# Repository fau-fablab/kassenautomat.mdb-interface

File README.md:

kassenautomat.mdb-interface
===========================

MDB to USB Interface für Münzwechsler-Ansteuerung

FTDI-Konfiguration
------------------
 * es kommt ein FT232RL zum Einsatz
 * Tool für Linux: https://github.com/mehlis/ft232r_prog.git
 * sonst FT_PROG
 * Linuxzeile: `./ft232r_prog --product 'MDB Interface' --manufacturer 'FAU FabLab' --cbus0 TxLED --cbus1 RxLED --cbus2 Clk12`

Atmel
-----
  * `make fuse` (zur Zeit für external clock via FTDI)
  *  http://www.engbedded.com/fusecalc/
  *  Wenn die Fuses auf externen Takt gesetzt sind, läuft der Chip nur, solange kein USB suspend ist - screen offen halten! (wirklich? nicht jeder hat usb autosuspend an.)
  * `make program`

Sicherung 12V-Schiene
---------------------
  * im worst case sollte eine 5A mtltrg. Sicherung für die 12V-Schiene reichen

Aktueller Stand Platine
-----------------------
  * Kommunikation Atmel <-> PC -> MDB geht, MDB -> PC sollte in rev2 auch gehen.
  * RX- und TX-LEDs am FT232RL gehen nicht (TM)

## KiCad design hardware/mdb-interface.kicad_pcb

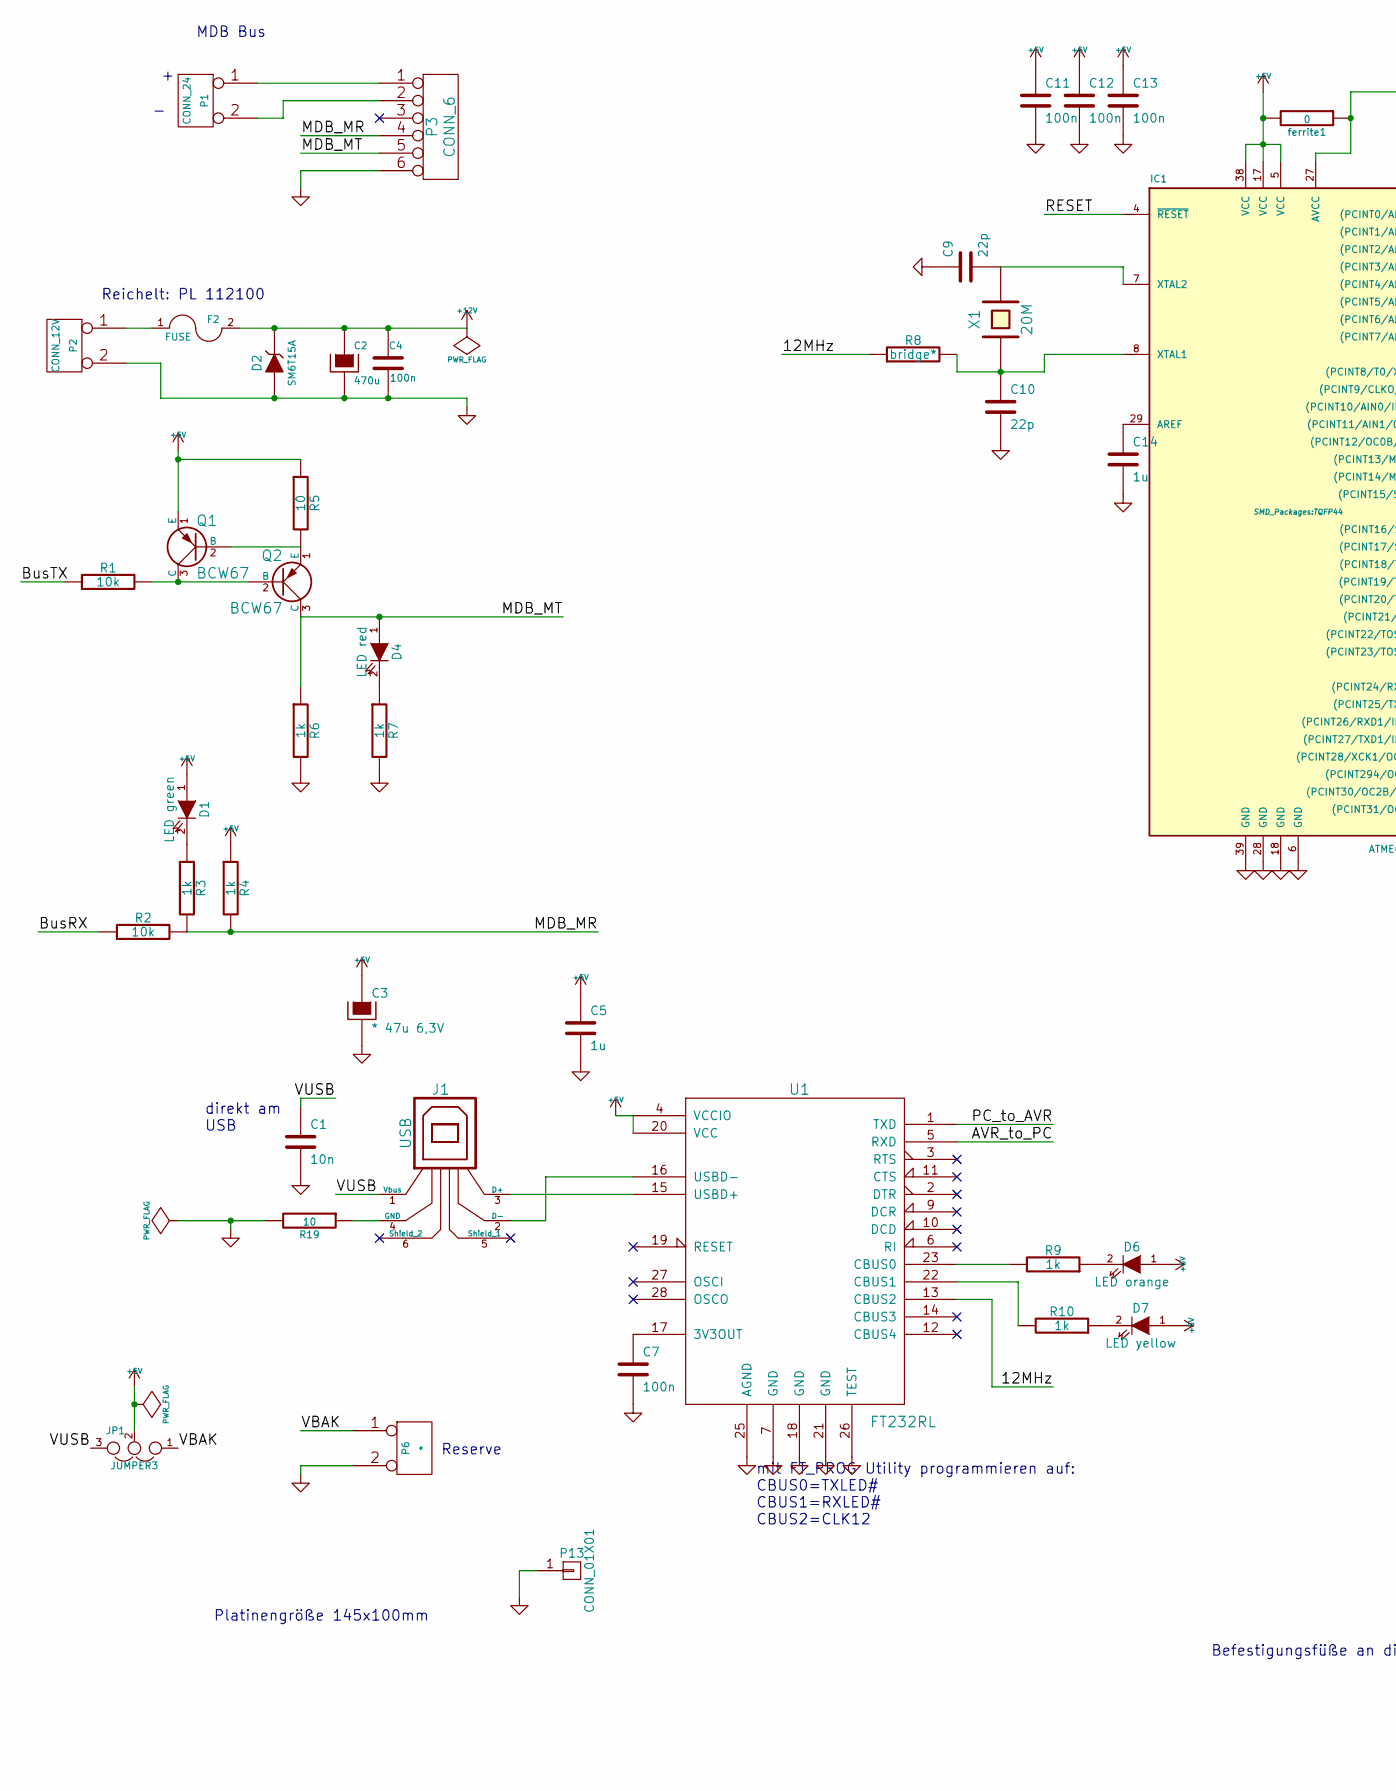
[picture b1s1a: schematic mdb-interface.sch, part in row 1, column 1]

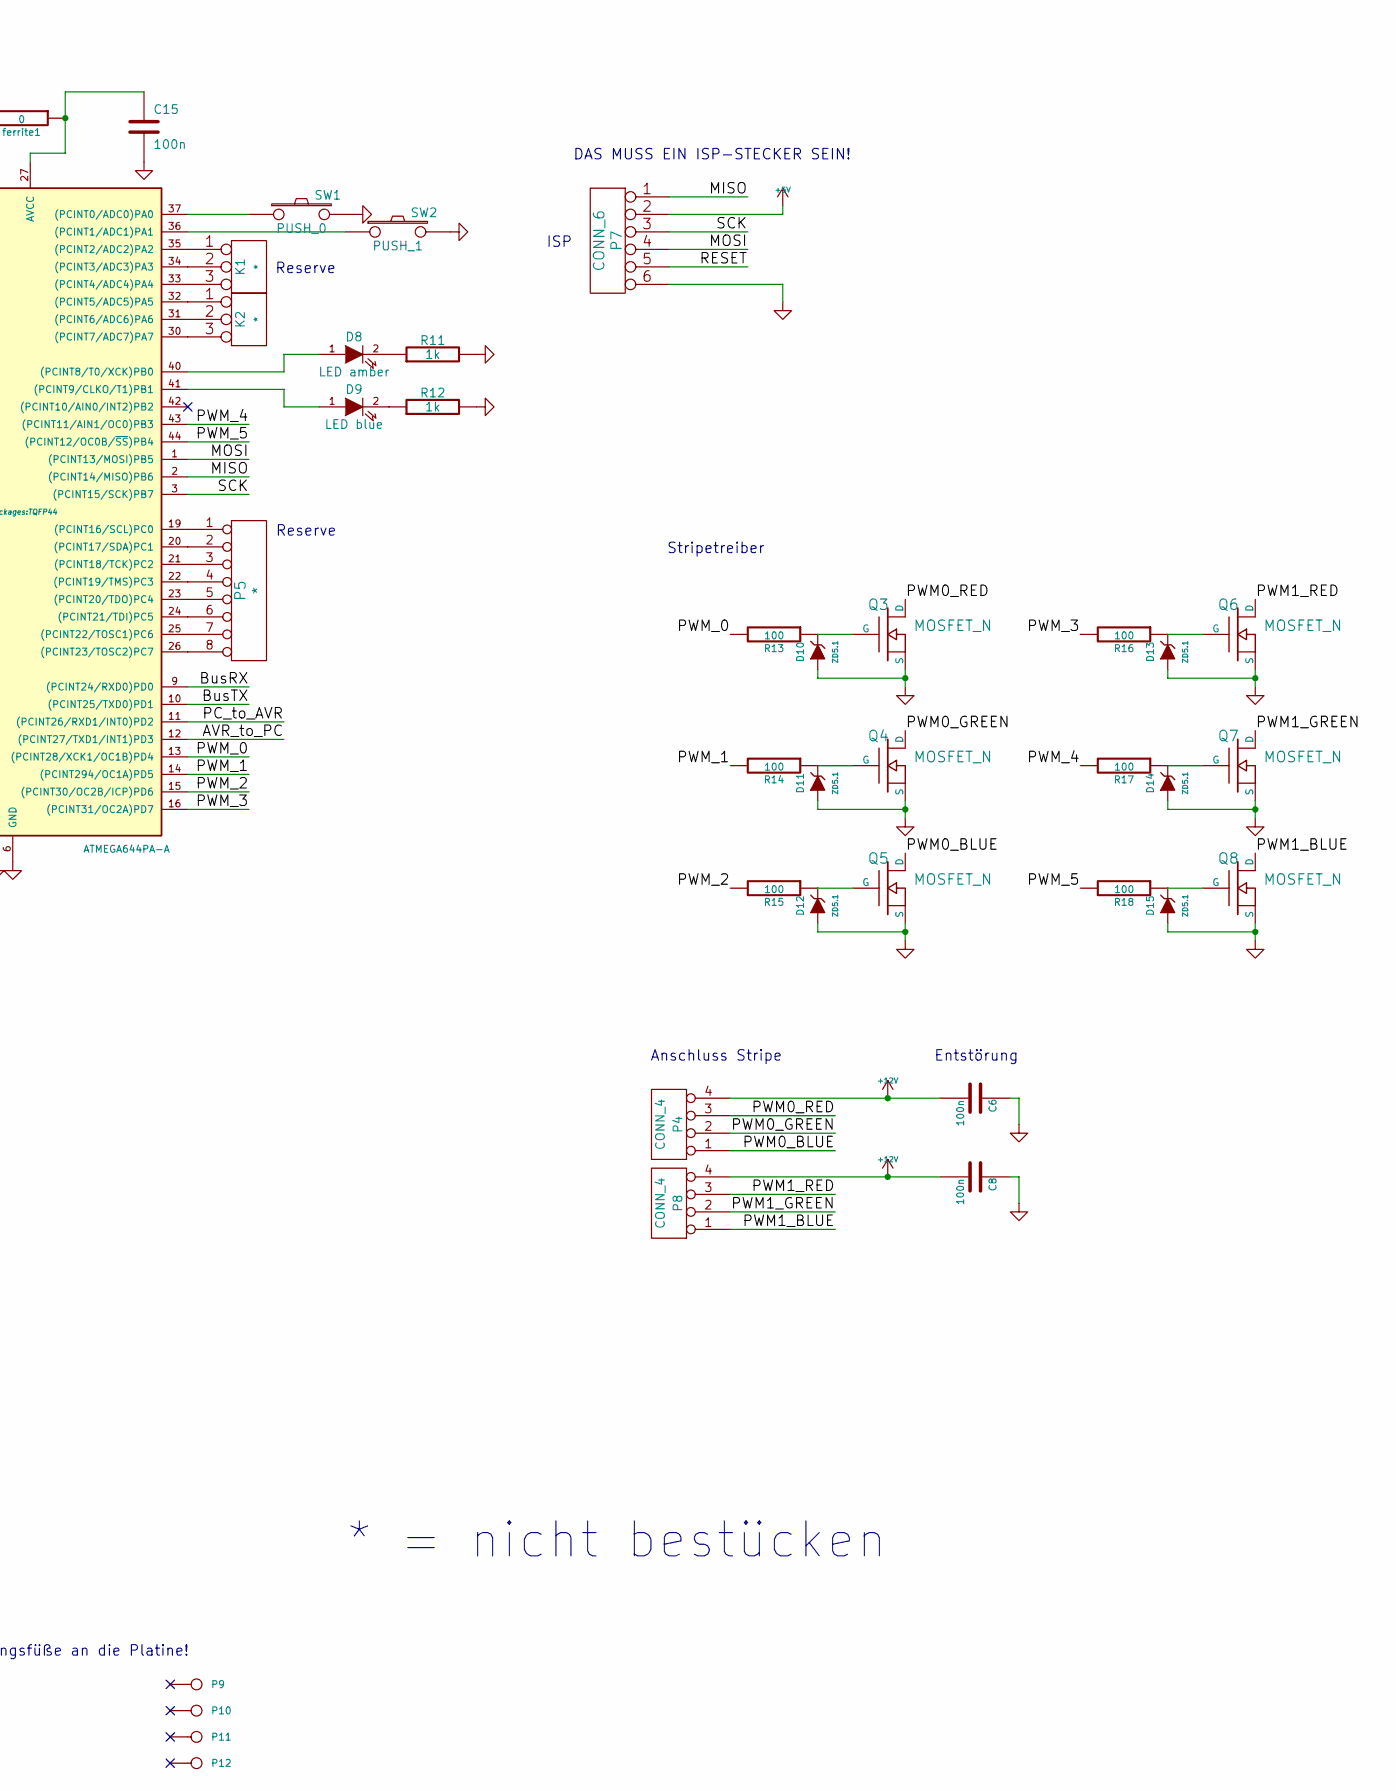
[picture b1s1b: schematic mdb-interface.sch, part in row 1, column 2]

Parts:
C1: 10n; SM0603_Capa
C2: 470u; Elko_vert_DM10_RM5_CopperClear
C3: * 47u 6,3V; c_elec_5x5.8
C4, C7, C11, C12, C13, C15: 100n; SM0603_Capa
C5, C14: 1u; c_0805
C6, C8: 100n; SM0805
C9, C10: 22p; c_0805
D1: LED green; LED-3MM
D2: SM6T15A; Diode-SMB_Standard
D4: LED red; LED-3MM
D6: LED orange; LED-3MM
D7: LED yellow; LED-3MM
D8: LED amber; LED-3MM
D9: LED blue; LED-3MM
D10, D11, D12, D13, D14, D15: ZD5.1; Diode-MiniMELF_Standard
F2: FUSE; Fuseholder5x20_horiz_SemiClosed_Casing10x25mm
IC1: ATMEGA644PA-A; TQFP44
J1: USB; USB_B
JP1: JUMPER3; NetTie-II_SMD
K1, K2: *; PINHEAD1-3
P1: CONN_24; PINHEAD1-2
P2: CONN_12V; PINHEAD1-2
P3: CONN_6; PINHEAD1-6
P4, P8: CONN_4; SIL-4
P5: *; SIL-8
P6: *; SIL-2
P7: CONN_6; Pin_Header_Straight_2x03
P9, P10, P11, P12: CONN_1; MountingHole_3-7mm
P13: CONN_01X01; 1pin
Q1, Q2: BCW67; sot23
Q3, Q4, Q5, Q6, Q7, Q8: MOSFET_N; sot428
R1, R2: 10k; SM0603_Resistor
R3, R4, R6, R7, R9, R10, R11, R12: 1k; SM0603_Resistor
R5, R19: 10; SM0603_Resistor
R8: bridge*; SM0603_Resistor
R13, R14, R15, R16, R17, R18: 100; SM0603_Resistor
SW1: PUSH_0; SW_PUSH_SMALL
SW2: PUSH_1; SW_PUSH_SMALL
U1: FT232RL; SSOP28
X1: 20M; Q_49U3HMS
ferrite1: 0; SM0603_Resistor

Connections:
+12V: C2.1, C4.1, C6.2, C8.2, D2.2 (K), F2.2, P4.4, P8.4
/12MHz: R8.1, U1.13 (CBUS2)
/AVR_to_PC: IC1.12 ((PCINT27/TXD1/INT1)PD3), U1.5 (RXD)
/BusRX: IC1.9 ((PCINT24/RXD0)PD0), R2.1
/BusTX: IC1.10 ((PCINT25/TXD0)PD1), R1.1
/MDB_MR: P3.4, R2.2, R3.2, R4.2
/MDB_MT: D4.1 (A), P3.5, Q2.3 (C), R6.1
/MISO: IC1.2 ((PCINT14/MISO)PB6), P7.1
/MOSI: IC1.1 ((PCINT13/MOSI)PB5), P7.4
/PC_to_AVR: IC1.11 ((PCINT26/RXD1/INT0)PD2), U1.1 (TXD)
/PWM0_BLUE: P4.1, Q5.D
/PWM0_GREEN: P4.2, Q4.D
/PWM0_RED: P4.3, Q3.D
/PWM1_BLUE: P8.1, Q8.D
/PWM1_GREEN: P8.2, Q7.D
/PWM1_RED: P8.3, Q6.D
/PWM_0: IC1.13 ((PCINT28/XCK1/OC1B)PD4), R13.2
/PWM_1: IC1.14 ((PCINT294/OC1A)PD5), R14.2
/PWM_2: IC1.15 ((PCINT30/OC2B/ICP)PD6), R15.2
/PWM_3: IC1.16 ((PCINT31/OC2A)PD7), R16.2
/PWM_4: IC1.43 ((PCINT11/AIN1/OC0)PB3), R17.2
/PWM_5: IC1.44 ((PCINT12/OC0B/~SS~)PB4), R18.2
/RESET: IC1.4 (~RESET), P7.5
/SCK: IC1.3 ((PCINT15/SCK)PB7), P7.3
/VBAK: JP1.1, P6.1
/VUSB: C1.1, J1.1 (Vbus), JP1.3
GND: C1.2, C2.2, C3.2, C4.2, C5.2, C6.1, C7.2, C8.1, C9.1, C10.2, C11.2, C12.2, C13.2, C14.2, C15.2, D2.1 (A), D10.1 (A), D11.1 (A), D12.1 (A), D13.1 (A), D14.1 (A), D15.1 (A), IC1.6 (GND), IC1.18 (GND), IC1.28 (GND), IC1.39 (GND), P2.2 (PM), P3.6, P6.2 (PM), P7.6, P13.1, Q3.S, Q4.S, Q5.S, Q6.S, Q7.S, Q8.S, R6.2, R7.2, R11.2, R12.2, R19.2, SW1.2, SW2.2, U1.7 (GND), U1.18 (GND), U1.21 (GND), U1.25 (AGND), U1.26 (TEST)
unnamed: C7.1, U1.17 (3V3OUT)
unnamed: C9.2, IC1.7 (XTAL2), X1.2
unnamed: C10.1, IC1.8 (XTAL1), R8.2, X1.1
unnamed: C14.1, IC1.29 (AREF)
unnamed: C15.1, IC1.27 (AVCC), ferrite1.1
unnamed: D1.2 (K), R3.1
unnamed: D4.2 (K), R7.1
unnamed: D6.2 (K), R9.1
unnamed: D7.2 (K), R10.1
unnamed: D8.1 (A), IC1.40 ((PCINT8/T0/XCK)PB0)
unnamed: D8.2 (K), R11.1
unnamed: D9.1 (A), IC1.41 ((PCINT9/CLKO/T1)PB1)
unnamed: D9.2 (K), R12.1
unnamed: D10.2 (K), Q3.G, R13.1
unnamed: D11.2 (K), Q4.G, R14.1
unnamed: D12.2 (K), Q5.G, R15.1
unnamed: D13.2 (K), Q6.G, R16.1
unnamed: D14.2 (K), Q7.G, R17.1
unnamed: D15.2 (K), Q8.G, R18.1
unnamed: F2.1, P2.1
unnamed: IC1.19 ((PCINT16/SCL)PC0), P5.1
unnamed: IC1.20 ((PCINT17/SDA)PC1), P5.2
unnamed: IC1.21 ((PCINT18/TCK)PC2), P5.3
unnamed: IC1.22 ((PCINT19/TMS)PC3), P5.4
unnamed: IC1.23 ((PCINT20/TDO)PC4), P5.5
unnamed: IC1.24 ((PCINT21/TDI)PC5), P5.6
unnamed: IC1.25 ((PCINT22/TOSC1)PC6), P5.7
unnamed: IC1.26 ((PCINT23/TOSC2)PC7), P5.8
unnamed: IC1.30 ((PCINT7/ADC7)PA7), K2.3
unnamed: IC1.31 ((PCINT6/ADC6)PA6), K2.2 (PM)
unnamed: IC1.32 ((PCINT5/ADC5)PA5), K2.1
unnamed: IC1.33 ((PCINT4/ADC4)PA4), K1.3
unnamed: IC1.34 ((PCINT3/ADC3)PA3), K1.2 (PM)
unnamed: IC1.35 ((PCINT2/ADC2)PA2), K1.1
unnamed: IC1.36 ((PCINT1/ADC1)PA1), SW2.1
unnamed: IC1.37 ((PCINT0/ADC0)PA0), SW1.1
unnamed: J1.2 (D-), U1.16 (USBD-)
unnamed: J1.3 (D+), U1.15 (USBD+)
unnamed: J1.4 (GND), R19.1
unnamed: P1.1, P3.1
unnamed: P1.2 (PM), P3.2
unnamed: R9.2, U1.23 (CBUS0)
unnamed: R10.2, U1.22 (CBUS1)

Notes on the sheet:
* = nicht bestücken
ISP
Reserve
mit FT_PROG Utility programmieren auf: CBUS0=TXLED# CBUS1=RXLED# CBUS2=CLK12
direkt am USB
MDB Bus
Stripetreiber
Anschluss Stripe
Reichelt: PL 112100
Befestigungsfüße an die Platine!
DAS MUSS EIN ISP-STECKER SEIN!
Platinengröße 145x100mm
Entstörung

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
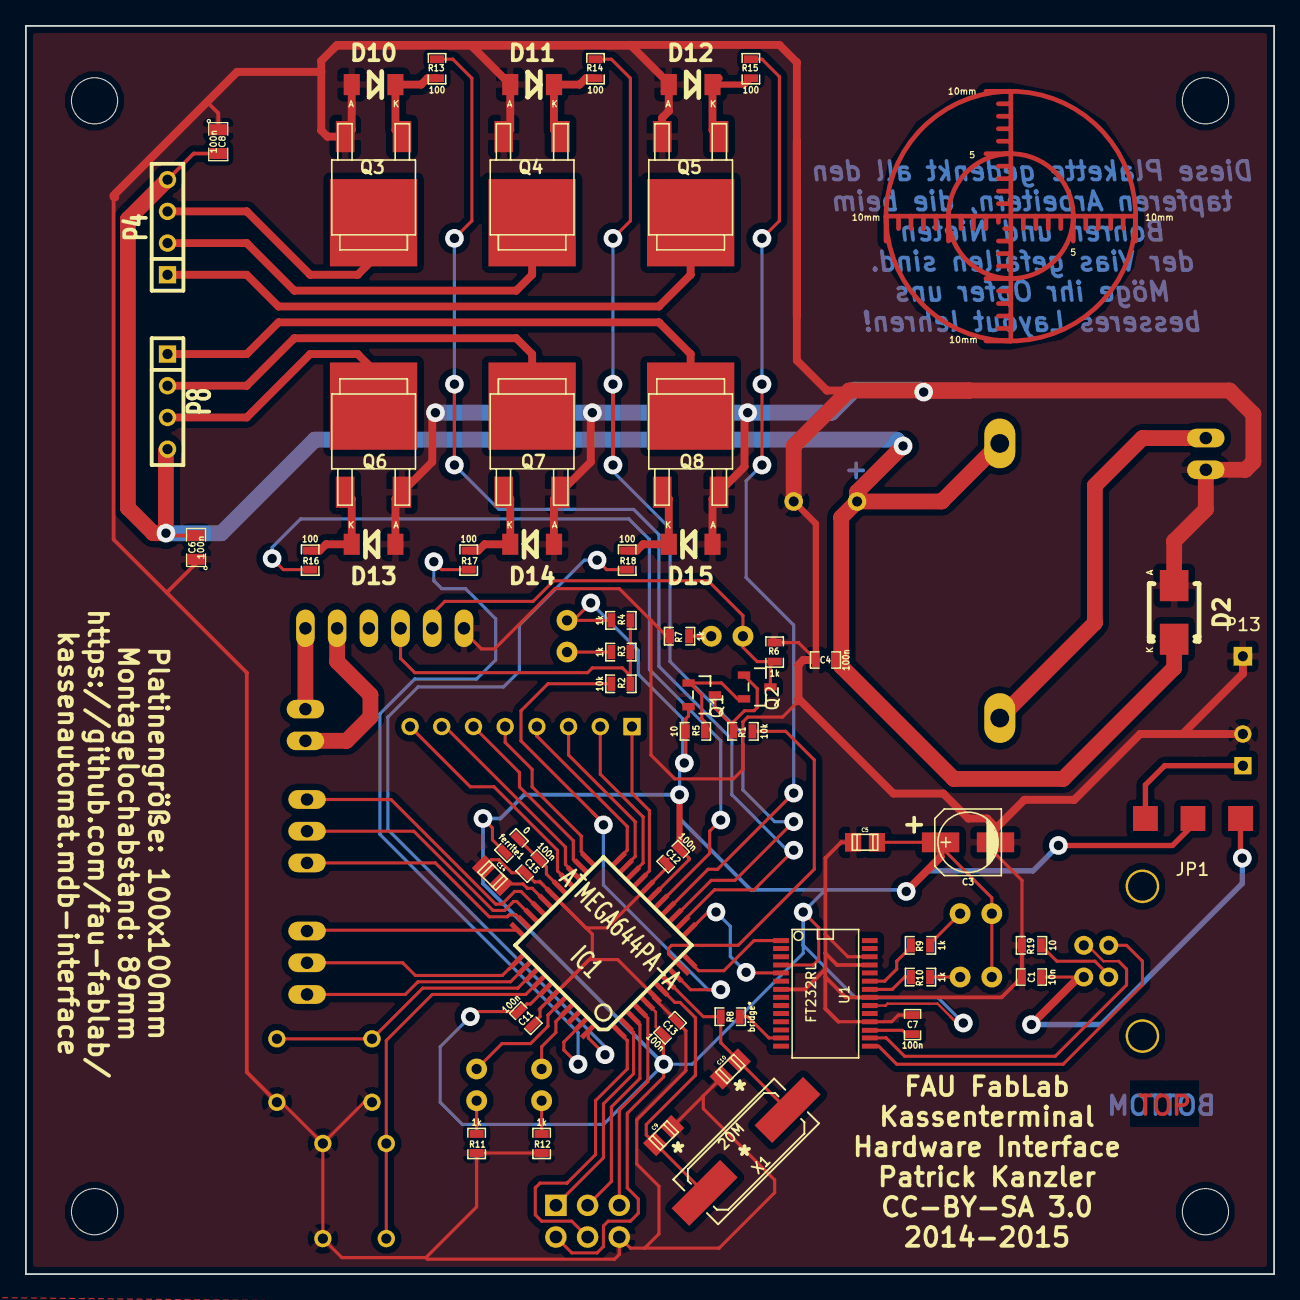
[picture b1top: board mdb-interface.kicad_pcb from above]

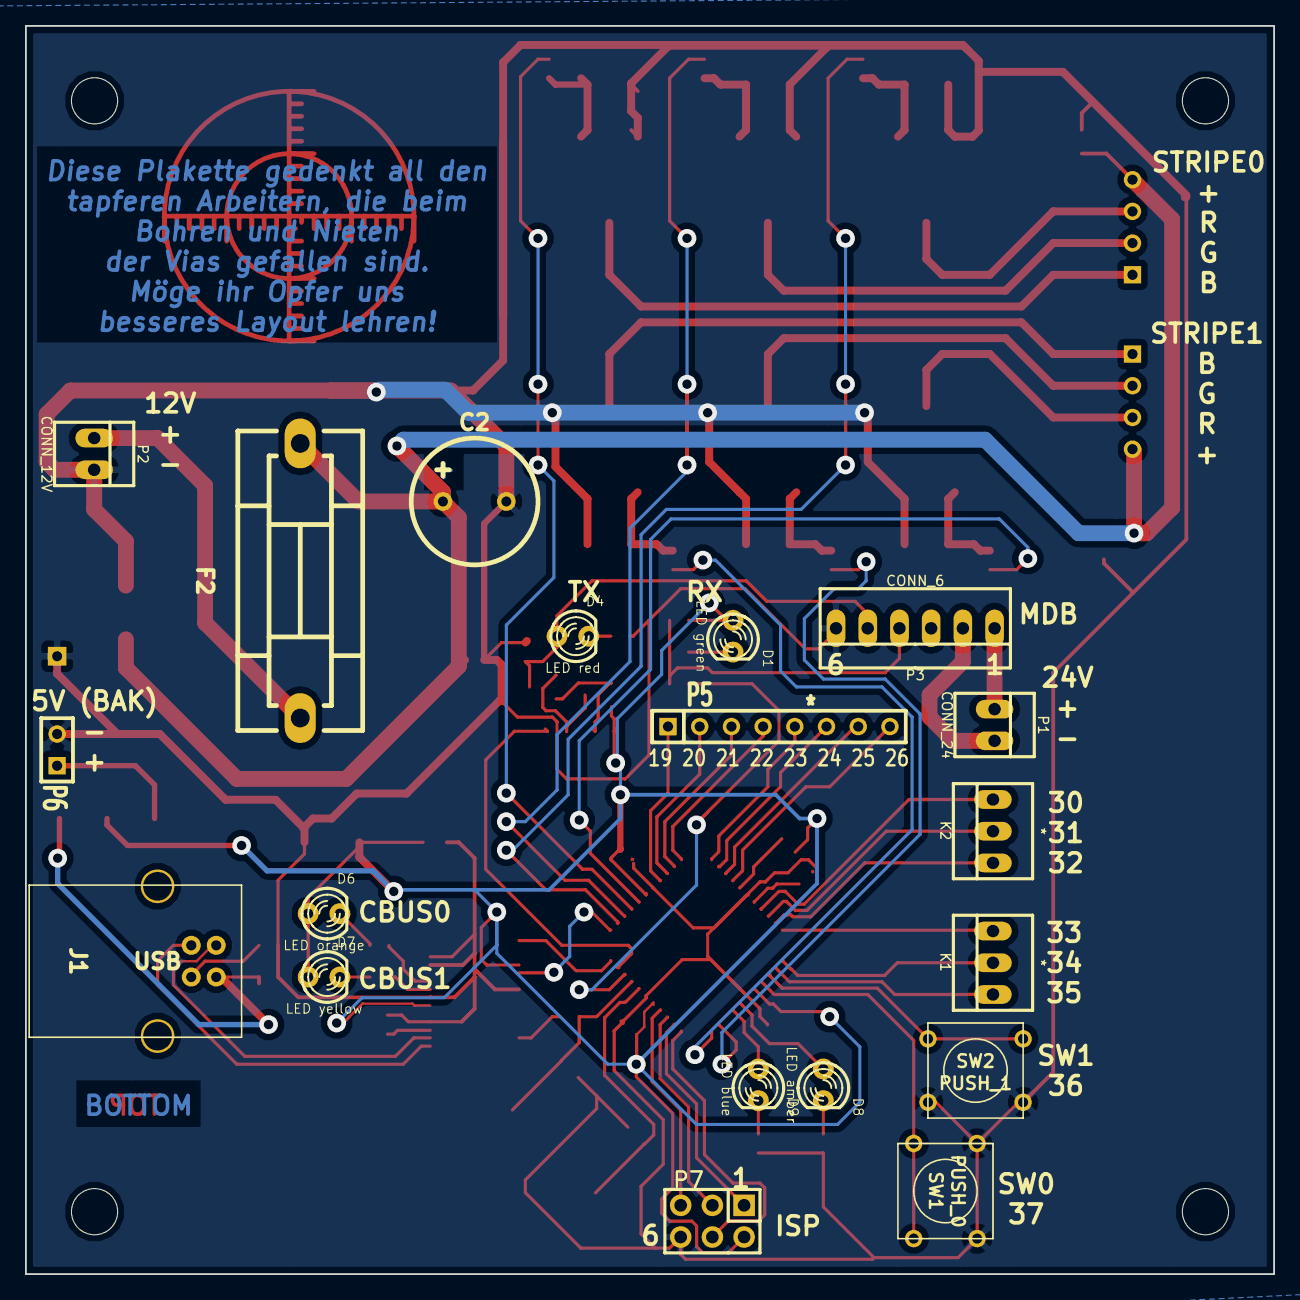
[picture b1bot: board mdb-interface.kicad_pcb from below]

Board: 2 copper layers, 100.0 x 100.0 mm, 80 parts (19 on the bottom side), 73 nets.

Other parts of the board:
MSC: Gauge_10mm_Type5_CopperTop_RevA_Date22Jun2010; Gauge_10mm_Type5_CopperTop

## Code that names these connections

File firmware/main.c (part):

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
#define LED_DDR DDRB				// Hier DDR der Test-LED einstellen!
#define LED_PORT PORTB				// Hier PORT der Test-LED einstellen!
#define LED_AMBER_PIN PB0				// Hier PIN der Test-LED einstellen!
#define LED_BLUE_PIN PB1
#define LED_AMBER(x) out(LED_PORT,LED_AMBER_PIN,0,x)	// DO NOT CHANGE
#define LED_BLUE(x) out(LED_PORT,LED_BLUE_PIN,0,x)	// DO NOT CHANGE

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	uartBus_init();
        hopper_init();
	// UART DDRs:
	DDRD |= (1<<PD3) | (1<<PD1);
        
        
        // RGB LEDs switched on at start, later overriden by timer PWM output
        DDRD |= (1<<PD4) | (1<<PD5) | (1<<PD6) | (1<<PD7);
//  	PORTD |= (1<<PD4) | (1<<PD5) | (1<<PD6) | (1<<PD7);
        DDRB |= (1<<PB3) | (1<<PB4);
//           PORTB |= (1<<PB3) | (1<<PB4);
        init_timer();
	// send one byte so that txReady() works
	uartPC_tx('\n');
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
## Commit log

2014-09-26 firmware
2014-09-26 different licensing for firmware and hardware
2014-09-27 FT232RL
2014-09-27 Update LICENSE
    Lizenz für Hardware hinzugefügt
2014-09-28 Hardware für Board hinzugefügt, fixes #1
2014-09-28 grundlegende Konfiguration, um das Board verwenden zu können
2014-09-28 README: Notiz zum Programmieren mit richtiger Geschwindigkeit hinzugefügt
2014-09-28 repair DDRs and UART definitions. Fixes #2.
2014-09-28 README: Fix indendation
2014-09-29 Fuse for 12V determined, fixes #5
2014-09-29 Notizen
2014-10-01 Notizen zum aktuellen Stand
2014-10-10 fix UART
2014-12-20 cleanup
2015-01-18 added missing footprint
2015-01-18 MDB_MR PULL-Up statt Pull-Down. fixes #10 falls die Diode passt
2015-01-18 lötbrücke für 5V hinzugefügt, fixes #13
2015-01-18 extra GND Pin, fixes #12
2015-01-18 added schematic symbol for PNP with swapped leads, fixes #9
2015-01-18 version bump
2015-01-18 Leiterplattenbemaßung gesäubert, fixes #14
2015-01-18 Platine angepasst, bereit zur Fertigungsvorbereitung, fixes #11
2015-01-19 Platine aktualisiert: DRC stimmt jetzt für multi-cb und hat TOP/BOTTOM-Markierung
2015-01-26 Gerber-Daten erzeugt
2015-01-27 Gerber erzeugt
2015-01-27 zip-Archiv der gerber-Daten
2015-01-27 Bohrprogramm hat gefehlt
2015-04-20 RGB LED auf dauer-an
2015-05-02 moved mdb-interface to subdirectory
2015-05-03 first draft of connection interface to hopper
2015-05-03 circuit now with better couplers and fuse
2015-05-05 first real version of schematic
2015-05-05 added profet status line to connector to mdb-board
2015-05-05 add directory for the servopusher for the coin-device
2015-05-05 servopusher laser files added
2015-05-05 added nametag
2015-05-05 updated parts to be SMDable
2015-05-05 annotation
2015-05-05 added notice on how to connect to MDB-interface
2015-05-09 LED and hopper extension commands
2015-05-09 small improvements to LED and hopper
2015-05-09 fix errors
2015-05-09 remove warning
2015-05-12 fix LEDs, disable hopper because it is untested
2015-05-12 update datasheet
2015-06-14 fixed some issues with schematic
2015-06-14 added attiny to schematic
2015-06-15 minor fixes in schematic for Reichelt-order
2015-06-24 remove floating-point code to possibly improve speed (#22)
2015-06-24 convert Makefile to unix line endings
2015-07-06 save CPU time by only processing one RGB channel per task call (#22)
2016-06-17 ADD arduinofiles for the servopusher
2016-07-04 fix README.md layout
2016-07-04 add the faceplate for the unlocking-button
2016-07-05 Servodrehung angepasst
2017-05-25 Troubleshoot MDB resets: Print reset cause, set lower brownout level
2017-05-25 MDB Interface Platine: Änderungsnotiz zu 5V-Versorgung

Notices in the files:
firmware/main.c:
License: GPLv2 or later
Author: Copyright (C) Max Gaukler <development@maxgaukler.de>
This program is free software; you can redistribute it and/or modify
it under the terms of the GNU General Public License as published by
the Free Software Foundation; either version 2 of the License, or
(at your option) any later version.
hardware/mdb-interface.kicad_pcb:
CC-BY-SA 3.0
